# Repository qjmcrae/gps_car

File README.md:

# gps_car
Arduino Code for SLCC Slick Science GPS Car

Starting with version for hardware 7.0
Summer 2022 Slick Science

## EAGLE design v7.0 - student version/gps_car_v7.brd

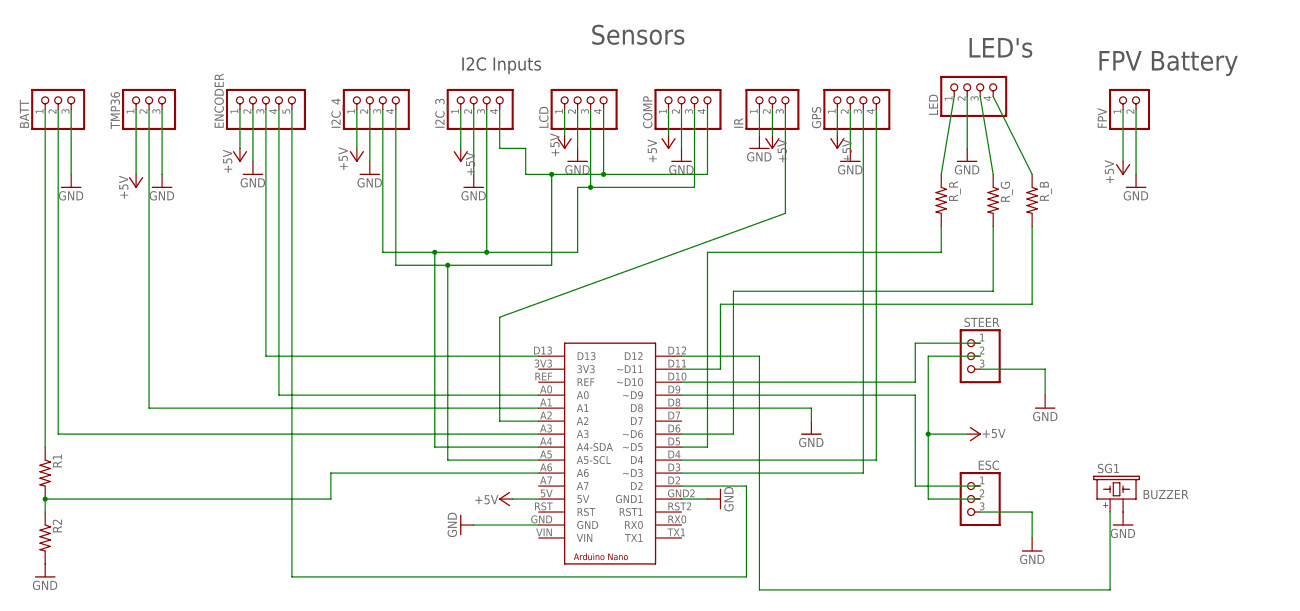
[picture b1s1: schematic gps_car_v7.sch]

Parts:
BATT: PINHD-1X3; 1X03
COMP: PINHD-1X4; 1X04
ENCODER: PINHD-1X5; 1X05
ESC: PINHD-1X3; 1X03
FPV: PINHD-1X2; 1X02
GPS: PINHD-1X4; 1X04
I2C_3, I2C_4: PINHD-1X4; 1X04
IR: PINHD-1X3; 1X03
LCD: PINHD-1X4; 1X04
LED: PINHD-1X41X04X2MM; 1_04X2MM
R1, R2: R-US_0204/2V; 0204V
R_B: R-US_0204/2V; 0204V
R_G: R-US_0204/2V; 0204V
R_R: R-US_0204/2V; 0204V
SG1: BUZZER; BUZZER-9MM-PTH
STEER: PINHD-1X3; 1X03
TMP36: PINHD-1X31X03/2MM; 1_03X2MM
U$1: NANO

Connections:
+5V: COMP.1, ENCODER.1, ESC.2, FPV.1, GPS.1, I2C_3.1, I2C_4.1, IR.2, LCD.1, STEER.2, TMP36.1, U$1.5V
BAT_1: BATT.2, U$1.A3
BAT_2: BATT.1, R1.1
GND: BATT.3, COMP.2, ENCODER.2, ESC.3, FPV.2, GPS.2, I2C_3.2, I2C_4.2, IR.1, LCD.2, LED.2, R2.2, SG1.P$2 (2), STEER.3, TMP36.3, U$1.D8, U$1.GND, U$1.GND2 (GND1)
unnamed: ESC.1, U$1.D9 (~D9)
unnamed: R_B.2, U$1.D11 (~D11)
unnamed: ENCODER.3, U$1.D13
unnamed: GPS.3, U$1.D3 (~D3)
unnamed: GPS.4, U$1.D4
unnamed: ENCODER.5, U$1.D2
unnamed: LED.1, R_R.1
unnamed: ENCODER.4, U$1.A0
unnamed: TMP36.2, U$1.A1
unnamed: SG1.P$1 (1), U$1.D12
unnamed: LED.3, R_G.1
unnamed: LED.4, R_B.1
unnamed: R1.2, R2.1, U$1.A6
unnamed: R_R.2, U$1.D5 (~D5)
unnamed: STEER.1, U$1.D10 (~D10)
unnamed: R_G.2, U$1.D6 (~D6)
unnamed: IR.3, U$1.A2
SCL: COMP.4, I2C_3.4, I2C_4.4, LCD.4, U$1.A5 (A5-SCL)
SDA: COMP.3, I2C_3.3, I2C_4.3, LCD.3, U$1.A4 (A4-SDA)

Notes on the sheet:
Sensors
LED's
I2C Inputs
FPV Battery

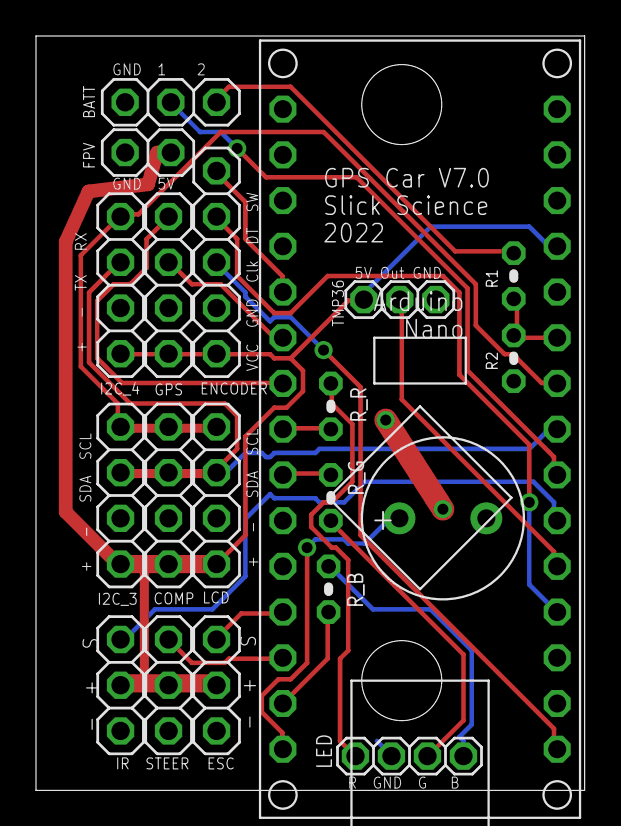
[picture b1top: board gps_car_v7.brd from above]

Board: 2 copper layers, 30.5 x 41.9 mm, 20 parts (0 on the bottom side), 23 nets.
